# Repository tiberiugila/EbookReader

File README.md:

# OpenBook E-Reader

## Overview
OpenBook is a cutting-edge electronic reading device built around the ESP32-C6 microcontroller. This sophisticated gadget integrates multiple sensors and interfaces to deliver an energy-efficient reading experience with extended functionality.

## Project Gallery
The project includes various design views that showcase:
- Device exploded assembly view
- PCB layout visualization
- Component arrangement
- 3D model renderings
- Enclosure design details

## Components List (BOM)

| Componenta | Link achizitie | Link datasheet |
|-----------|----------------|----------------|
| 112A-TAAR-R03 ATTEND | https://store.comet.srl.ro/Catalogue/Product/43497/ | https://www.snapeda.com/parts/112A-TAAR-R03/Attend/datasheet/ |
| BD5229G-TR | https://www.digikey.com/en/products/detail/rohm-semiconductor/BD5229G-TR/3663792 | https://fscdn.rohm.com/en/products/databook/datasheet/ic/power/voltage_detector/bd52xxg-e.pdf |
| ESP32 WROVER BME680 Sensor | https://store.comet.srl.ro/Catalogue/Product/50164/ | https://www.bosch-sensortec.com/media/boschsensortec/downloads/datasheets/bst-bme680-ds001.pdf |
| LED CHG_LED | https://ro.mouser.com/ProductDetail/Kingbright/KP-1608SURCK?qs=2JU0tDl2GZ3FuyEWfBV1%2Fg== | https://www.snapeda.com/parts/KP-1608SURCK/Kingbright/datasheet/ |
| Condensator C0402 | https://ro.mouser.com/c/passive-components/capacitors/ceramic-capacitors/?q=CC0402 | https://componentsearchengine.com/Datasheets/2/CC0402MRX5R5BB106.pdf |
| Condensator Tant | https://ro.mouser.com/ProductDetail/KYOCERA-AVX/TAJW107M010RNJ?qs=Wtp%252Bf%2FAeVqIH8v1VxV%252B1Rg%3D%3D | https://ro.mouser.com/datasheet/2/40/TAJ-3165264.pdf |
| Q1 DMG2305UX-7 | https://www.digikey.com/en/products/detail/diodes-incorporated/DMG2305UX-7/4340666 | https://www.diodes.com/assets/Datasheets/DMG2305UX.pdf |
| RTC MODULE DS3231SN# | https://www.snapeda.com/parts/DS3231SN%23/Analog+Devices/view-part/?ref=eda | https://www.snapeda.com/parts/DS3231SN%23/Analog%20Devices/datasheet/ |
| ESP32 C6 WROOM-1-N8 | https://ro.mouser.com/ProductDetail/Espressif-Systems/ESP32-C6-WROOM-1-N8?qs=8Wlm6%252BaMh8ST02Gmwp74cw%3D%3D | https://www.snapeda.com/parts/ESP32-C6-WROOM-1-N8/Espressif%20Systems/datasheet/ |
| FH34SRJ-24S-0.5SH(99) | https://ro.mouser.com/ProductDetail/Hirose-Connector/FH34SRJ-24S-0.5SH99?qs=vcbW%252B4%252BSTIpKBl5ap9J8Fw%3D%3D | https://www.snapeda.com/parts/FH34SRJ-24S-0.5SH(99)/Hirose%20Connector/datasheet/ |
| MAX 17048G+T10 | https://www.snapeda.com/parts/MAX17048G+T10/Analog+Devices/view-part/?ref=eda | https://www.snapeda.com/parts/MAX17048G+T10/Analog%20Devices/datasheet/ |
| MBR0530 Schottky Diode | https://www.snapeda.com/parts/MBR0530/Onsemi/view-part/?ref=snap | https://www.snapeda.com/parts/MBR0530/ON%20Semiconductor/datasheet/ |
| MCP73831 Power Management | https://www.snapeda.com/parts/MCP73831T-2ACI/OT/Microchip/datasheet/ | https://www.snapeda.com/parts/MCP73831T-2ACI/OT/Microchip/datasheet/ |
| PFMF.050.1 | https://ro.mouser.com/ProductDetail/EPCOS-TDK/B72520T0350K062?qs=dEfas%2FXlABIszF52uu7vrg%3D%3D | https://www.tdk-electronics.tdk.com/inf/75/db/CTVS_14/Surge_protection_series.pdf |
| PGB1010603MR | https://www.snapeda.com/parts/PGB1010603MR/Littelfuse/view-part/?ref=eda | https://www.snapeda.com/parts/PGB1010603MR/Littelfuse%20Inc./datasheet/ |
| QWIIC_RIGHT_ANGLE CONNECTOR | https://ro.mouser.com/ProductDetail/SparkFun/PRT-14417?qs=wd5RIQLrsJhgdz%2FpmZ%2F3GQ== | https://ro.mouser.com/datasheet/2/813/Qwiic_Connector_Datasheet-1223982.pdf |
| Rezistenta R0402 | https://grabcad.com/library/resistor-0402-1) | https://www.yageo.com/upload/media/product/products/datasheet/rchip/PYu-RC_Group_51_RoHS_L_12.pdf |
| SD0805S020S1R0 | https://ro.mouser.com/ProductDetail/KYOCERA-AVX/SD0805S020S1R0?qs=jCA%252BPfw4LHbpkAoSnwrdjw%3D%3D | https://ro.mouser.com/datasheet/2/40/schottky-3165252.pdf |
| Si1308EDL-T1-GE3 MOSFET | https://www.snapeda.com/parts/SI1308EDL-T1-GE3/Vishay+Siliconix/view-part/?welcome=home&ref=eda | https://www.snapeda.com/parts/SI1308EDL-T1-GE3/Vishay%20Siliconix/datasheet/ |
| USB4110-GF-A | https://ro.mouser.com/ProductDetail/GCT/USB4110-GF-A?qs=KUoIvG%2F9IlYiZvIXQjyJeA%3D%3D | https://ro.mouser.com/datasheet/2/837/GCT_USB4110_Product_Drawing___20k_cycles-3455479.pdf |
| USBLC6-2SC6Y | https://ro.mouser.com/ProductDetail/STMicroelectronics/USBLC6-2SC6Y?qs=gNDSiZmRJS%2FOgDexvXkdow%3D%3D | https://ro.mouser.com/datasheet/2/389/usblc6_2sc6y-1852505.pdf |
| W25Q512JVEIQ | https://www.snapeda.com/parts/W25Q512JVEIQ/Winbond+Electronics/view-part/?ref=eda | https://www.winbond.com/resource-files/W25Q512JV%20SPI%20RevB%2006252019%20KMS.pdf |
| XC6220A331MR-G | https://componentsearchengine.com/part-view/XC6220A331MR-G/Torex | https://product.torexsemi.com/system/files/series/xc6220.pdf |
| 744043680 BOBINA | https://ro.mouser.com/ProductDetail/Wurth-Elektronik/744043680?qs=PGXP4M47uW6VkZq%252BkzjrHA%3D%3D | https://www.we-online.com/components/products/datasheet/744043680.pdf |

## Hardware Capabilities

### Processing & Connectivity
The ESP32-C6 serves as the heart of OpenBook, providing Wi-Fi 6 and Bluetooth 5.0 LE connectivity. Its extensive GPIO capabilities enable seamless integration with various peripheral components.

### Display Technology
The e-paper display connects through an SPI interface and utilizes the BD5229G-TR driver for voltage management. MOSFET-controlled power distribution enables complete shutdown when not in use, significantly enhancing energy efficiency.

### Environmental Monitoring
The BME688 sensor delivers comprehensive environmental data including temperature, humidity, barometric pressure, and air quality (VOC) readings via I2C interface.

### Power Systems
The device features:
- MCP73831-based charging circuit supporting up to 500mA charging current
- MAX17048G+T10 battery monitoring system providing detailed charge level information
- Energy-efficient design for extended reading time

## ESP32-C6 Pin Allocation

| Component         | Connected Pins      | Protocol | Function                               |
|-------------------|---------------------|----------|----------------------------------------|
| E-Paper Display   | IO12, IO11, IO5, IO4| SPI      | Display control and reset              |
| BME688 Sensor     | IO8, IO10           | I2C      | Environmental monitoring               |
| SD Card Interface | IO7                 | SPI      | External storage                       |
| RTC Module        | IO8, IO10           | I2C      | Real-time clock (shared I2C bus)       |
| USB Interface     | IO16, IO17          | UART     | Programming and debugging              |

## Implementation Process

1. Electronic schematic design and ESP32-C6 component integration
2. 2D layout development and component placement
3. Signal and power trace routing
4. Ground plane implementation on both PCB layers
5. Trace width and clearance rule application
6. Strategic connector positioning (Qwiic, USB-C)
7. Test pad placement for debugging
8. 3D model generation and mechanical compatibility verification

## Technical Notes

- Test points have been strategically positioned near board edges and critical components for easy access during testing and debugging
- Surface-mount diode pad sizes were adjusted from initial specifications to ensure reliable electrical connections and easier assembly
- Trace routing utilizes both top and bottom PCB layers for efficient signal and power distribution
- Ground planes have been implemented on both layers to optimize electrical performance

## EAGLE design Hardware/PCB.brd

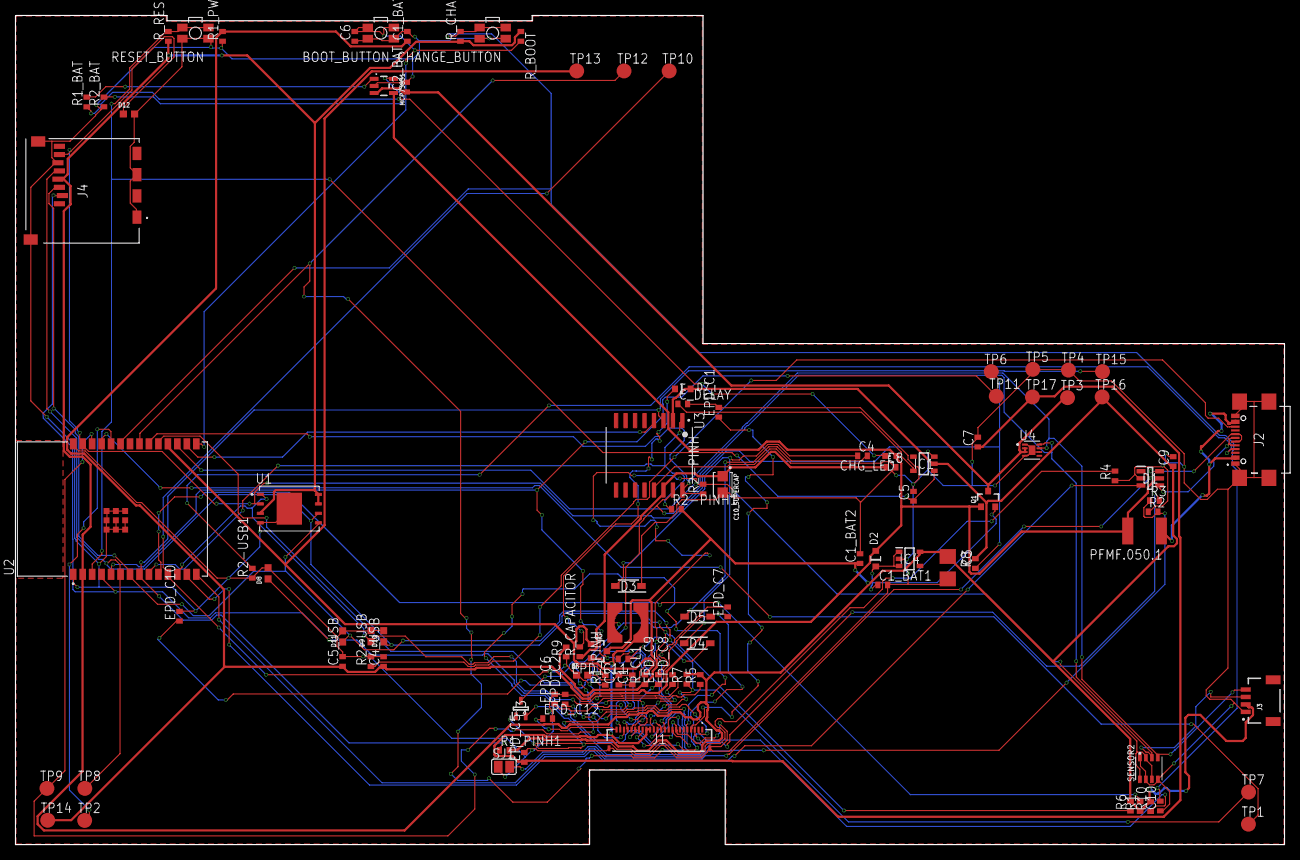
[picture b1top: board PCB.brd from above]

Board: 2 copper layers, 170.2 x 111.2 mm, 103 parts (0 on the bottom side), 55 nets.

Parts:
BOOT_BUTTON: BUTTON_CUSYOMV1; MYBUTTON
C1, C2, C6, C8, C10: 100nF; ESP32_WROVER_EAGLE-LTSPICE_C0402
C1_BAT, C2_BAT: 4.7uF; ESP32_WROVER_EAGLE-LTSPICE_C0402
C1_BAT1: 4.7 uF; EAGLE-LTSPICE_C0402
C1_BAT2, C5_USB: 4.7uF; EAGLE-LTSPICE_C0402
C3: 100uF TANT; RCL_CT3528
C4: 4.7uF/25V; ESP32_WROVER_EAGLE-LTSPICE_C0402
C4_USB, C9: 100nF; EAGLE-LTSPICE_C0402
C5: 1uF; ESP32_WROVER_EAGLE-LTSPICE_C0402
C7: 10uF; ESP32_WROVER_EAGLE-LTSPICE_C0402
C10_SUPERCAP: CPH3225A; CAPCP3225X100N
CHANGE_BUTTON: BUTTON_CUSYOMV1; MYBUTTON
CHG_LED: ADAFRUIT_CHIP-LED0603
C_DELAY: 100nF; ESP32_WROVER_EAGLE-LTSPICE_C0402
D1: USBLC6-2SC6Y; SOT95P280X145-6N
D2: ESP32_WROVER_AVX---SD0805S020S1R0_AVX_SD0805S020S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; ESP32_WROVER_AVX---SD0805S020S1R0_AVX_SD0805S020S1R0_0
D3, D4, D5: MBR0530; SOD3716X135N
D6, D8, D9, D10, D11, D12: PGB1010603MR; DIOC1608X36N
D7: SD0805S020S1R0; ESP32_WROVER_AVX---SD0805S020S1R0_AVX_SD0805S020S1R0_0
EPD_C1, EPD_C2, EPD_C6, EPD_C7, EPD_C8, EPD_C9, EPD_C10, EPD_C11, EPD_C12: 1uF/50V; ESP32_WROVER_EAGLE-LTSPICE_C0402
EPD_C5: 0.1uF/50V; ESP32_WROVER_EAGLE-LTSPICE_C0402
IC1: BD5229G-TR; SOT95P280X125-5N
IC4: XC6220A331MR-G; SOT95P280X120-5N
J1: FH34SRJ-24S-0.5SH_99_; FH34SRJ24S05SH99
J2: SAMACSYS_PARTS_USB4110-GF-A; SAMACSYS_PARTS_USB4110GFA
J3: QWIIC_RIGHT_ANGLE; JST04_1MM_RA
J4: 112A-TAAR-R03_ATTEND; 112ATAARR03ATTEND
L1: 744043680IND_4828-WE-TPC_WRE; IND_4828-WE-TPC_WRE
MCP73831: ESP32_WROVER_SPARKFUN-IC-POWER_MCP73831; ESP32_WROVER_SPARKFUN-IC-POWER_SOT23-5
PFMF.050.1: ESP32C6_VARISTORCN1812; ESP32C6_VARISTOR_CT/CN1812
Q1, Q2: 20V/4.2A/52mΩ/1.4W; ESP32_WROVER_SPARKFUN-DISCRETESEMI_SOT23-3
Q3: SI1308EDL-T1-GE3; SOT65P210X110-3N
R1, R1_PINH, R1_PINH1, R2-PINH, R2-PINH1, R4, R5, R6, R7, R8, R9, R10: 10K; ESP32_WROVER_EAGLE-LTSPICE_R0402
R1_BAT: 200; ESP32_WROVER_EAGLE-LTSPICE_R0402
R1_PWRUSB: 100K; ESP32_WROVER_EAGLE-LTSPICE_R0402
R2: 2.2; ESP32_WROVER_EAGLE-LTSPICE_R0402
R2-USB, R2-USB1: 5k1; ESP32_WROVER_EAGLE-LTSPICE_R0402
R2_BAT: 2K; ESP32_WROVER_EAGLE-LTSPICE_R0402
R3: 0.47; ESP32_WROVER_EAGLE-LTSPICE_R0402
RESET_BUTTON: BUTTON_CUSYOMV1; MYBUTTON
R_BOOT: 10K; ESP32_WROVER_EAGLE-LTSPICE_R0402
R_CAPACITOR: 15; ESP32_WROVER_EAGLE-LTSPICE_R0402
R_CHANGE: 10K; ESP32_WROVER_EAGLE-LTSPICE_R0402
R_CL1: 10K; ESP32_WROVER_EAGLE-LTSPICE_R0402
R_RESET: 10K; ESP32_WROVER_EAGLE-LTSPICE_R0402
SENSOR2: BME688; ESP32_WROVER_BME680_PSON80P300X300X100-8N
SJ1: SJ
TP1, TP2, TP3, TP4, TP5, TP6, TP7, TP8, TP9, TP10, TP11, TP12, TP13, TP14, TP15, TP16, TP17: TPTP20R; TP20R
U1: W25Q512JVEIQ; SON127P600X800X80-9N
U2: ESP32-C6-WROOM-1-N8; XCVR_ESP32-C6-WROOM-1-N8
U3: DS3231SN#; SOIC127P1032X265-16N
U4: MAX17048G+T10; SON50P200X200X80-9N

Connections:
3V3: C1_BAT2.1, C3.+, C9.1, D7.2, IC1.2, IC4.5, J3.2, J4.P4, Q2.3, R1.1, R1_PINH1.2, R2-PINH1.2, R5.2, R6.2, R7.2, R8.2, R9.2, R10.2, R_BOOT.1, R_CHANGE.1, R_CL1.1, R_RESET.1, TP16.TP, U1.3, U1.7, U1.8, U2.2, U3.2
32KHZ: R2-PINH1.1, U2.9, U3.1
DN: D1.4, J2.A7, J2.B7
DP: D1.6, J2.A6, J2.B6
EPD_3V3: C7.1, EPD_C5.1, J1.15, J1.16, L1.2, Q2.2, TP17.TP
EPD_3V3_C: Q2.1, R_CL1.2, TP13.TP, U2.18
EPD_BUSY: J1.9, TP9.TP, U2.26
EPD_CS: D6.1, J1.12, R9.1, TP10.TP, U2.11
EPD_DC: J1.11, TP11.TP, U2.5
EPD_RST: J1.10, TP12.TP, U2.21
FLASH_CS: D9.1, R5.1, U1.1, U2.12
GDR: J1.2, Q3.1, R4.2
GND: BOOT_BUTTON.1, BOOT_BUTTON.2, C1.2, C1_BAT.2, C1_BAT1.2, C1_BAT2.2, C2.2, C2_BAT.2, C3.-, C4_USB.2, C5.2, C5_USB.2, C6.1, C7.2, C8.2, C9.2, C10.1, C10_SUPERCAP.2, CHANGE_BUTTON.1, CHANGE_BUTTON.2, C_DELAY.2, D1.2, D3.1, D6.2, D8.2, D9.2, D10.2, D11.2, D12.2, EPD_C1.2, EPD_C2.2, EPD_C5.2, EPD_C6.2, EPD_C7.2, EPD_C8.2, EPD_C9.2, EPD_C10.2, EPD_C11.2, EPD_C12.2, IC1.3, IC4.2, J1.8, J1.17, J1.MP1, J1.MP2, J2.A1, J2.A12, J2.B1, J2.B12, J2.MP1, J2.MP2, J2.MP3, J2.MP4, J3.1, J4.G1, J4.G2, J4.G3, J4.G4, J4.P6, MCP73831.2, R1_PWRUSB.1, R2.1, R2-USB.2, R2-USB1.1, R2_BAT.1, R4.1, RESET_BUTTON.1, RESET_BUTTON.2, SENSOR2.1, SENSOR2.5, SENSOR2.7, SJ1.1, TP4.TP, TP5.TP, U1.4, U1.9, U2.1, U2.28, U2.29_1, U2.29_2, U2.29_3, U2.29_4, U2.29_5, U2.29_6, U2.29_7, U2.29_8, U2.29_9, U3.13, U4.1, U4.4, U4.6, U4.9
GPIO8: R1.2, U2.10
I2C_PW: C1.1, C2.1, R1_PINH.2, R2-PINH.2, SENSOR2.2, SENSOR2.6, SENSOR2.8, U2.17
INT_RTC: R1_PINH1.1, TP15.TP, U2.8, U3.3
IO/BOOT: BOOT_BUTTON.3, BOOT_BUTTON.4, C6.2, R_BOOT.2, U2.15
IO/CHANGE: C10.2, CHANGE_BUTTON.3, CHANGE_BUTTON.4, R_CHANGE.2, U2.23
MISO: D12.1, J4.P7, R8.1, TP6.TP, U1.2, U2.27
MOSI: D11.1, J1.14, J4.P3, R7.1, TP7.TP, U1.5, U2.7
unnamed: J2.A5, R2-USB1.2
unnamed: J2.B5, R2-USB.1
unnamed: C4.1, D3.2, D4.1
unnamed: C1_BAT1.1, D2.1, IC4.1, IC4.3, Q1.2
unnamed: C_DELAY.1, IC1.5
unnamed: CHG_LED.C, R1_BAT.1
unnamed: MCP73831.1, R1_BAT.2
unnamed: MCP73831.5, R2_BAT.2
unnamed: EPD_C12.1, J1.24
unnamed: EPD_C6.1, J1.18
unnamed: EPD_C7.1, J1.19
unnamed: EPD_C8.1, J1.20
unnamed: EPD_C10.1, J1.22
unnamed: D7.1, R_CAPACITOR.2
unnamed: EPD_C2.1, J1.5
unnamed: EPD_C1.1, J1.4
PREVGH: D5.1, EPD_C9.1, J1.21
PREVGL: D4.2, EPD_C11.1, J1.23
RESE: J1.3, Q3.2, R3.2
RESE': R2.2, R3.1, SJ1.2
RESET: C5.1, IC1.1, RESET_BUTTON.3, RESET_BUTTON.4, R_RESET.2, U2.3
RTC_RST: U2.16, U3.4
RX: TP2.TP, U2.24
SCK: D10.1, J1.13, J4.P5, R6.1, TP8.TP, U1.6, U2.6
SCL: J3.4, R2-PINH.1, SENSOR2.4, U2.20, U3.16, U4.7
SDA: J3.3, R1_PINH.1, SENSOR2.3, U2.19, U3.15, U4.8
SRC: C4.2, D5.2, L1.1, Q3.3
SS_SD: D8.1, J4.P2, R10.1, U2.4
TX: TP1.TP, U2.25
USB_D+: D1.1, U2.14
USB_D-: D1.3, U2.13
VBAT: C2_BAT.1, MCP73831.3, Q1.3, TP3.TP, U4.2, U4.3
VBUS: C1_BAT.1, C4_USB.1, C5_USB.1, CHG_LED.A, D1.5, D2.2, MCP73831.4, PFMF.050.1.2, Q1.1, R1_PWRUSB.2, TP14.TP
VRTC: C8.1, C10_SUPERCAP.1, R_CAPACITOR.1, U3.14
VUSB: J2.A4, J2.A9, J2.B4, J2.B9, PFMF.050.1.1

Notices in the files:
parts and their libraries:
COPYRIGHT: Copyright (C) 2024 Ultra Librarian. All rights reserved.
